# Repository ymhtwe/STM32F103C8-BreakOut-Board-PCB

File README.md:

# STM32F103C8-BreakOut-Board-PCB 

This repository contains the design files for a breakout board for the STM32F103C8T6 microcontroller in a 48-pin LQFP package. The breakout board provides easy access to all the pins of the microcontroller, as well as a USB-to-serial converter for programming and debugging.

Features
Compact breakout board for the STM32F103C8T6 microcontroller
All pins of the microcontroller are accessible via headers
Onboard 3.3V voltage regulator and decoupling capacitors
USB-to-serial converter for programming and debugging
Bootloader mode for easy firmware updates
Getting started
To get started with the STM32F103C8 Breakout Board PCB, you will need the following:

STM32F103C8T6 microcontroller (not included)
USB-to-serial cable (not included)
Development environment (e.g., STM32CubeIDE, Keil, or Arduino IDE)
To program and debug the microcontroller, connect the USB-to-serial cable to the J1 header on the breakout board, and connect the other end of the cable to your computer. Open your development environment and select the appropriate settings for the microcontroller and programming interface. You can then program and debug your firmware as usual.

Repository contents
Gerber/: Gerber files for manufacturing the PCB
Schematic/: Schematic and BOM for the PCB design
Hardware/: PCB layout design files in KiCad format
License
The STM32F103C8 Breakout Board PCB is released under the MIT License. See the LICENSE file for more details.

Credits
The STM32F103C8 Breakout Board PCB was designed by Ye Min Htwe. If you have any questions or feedback, please open an issue on GitHub.

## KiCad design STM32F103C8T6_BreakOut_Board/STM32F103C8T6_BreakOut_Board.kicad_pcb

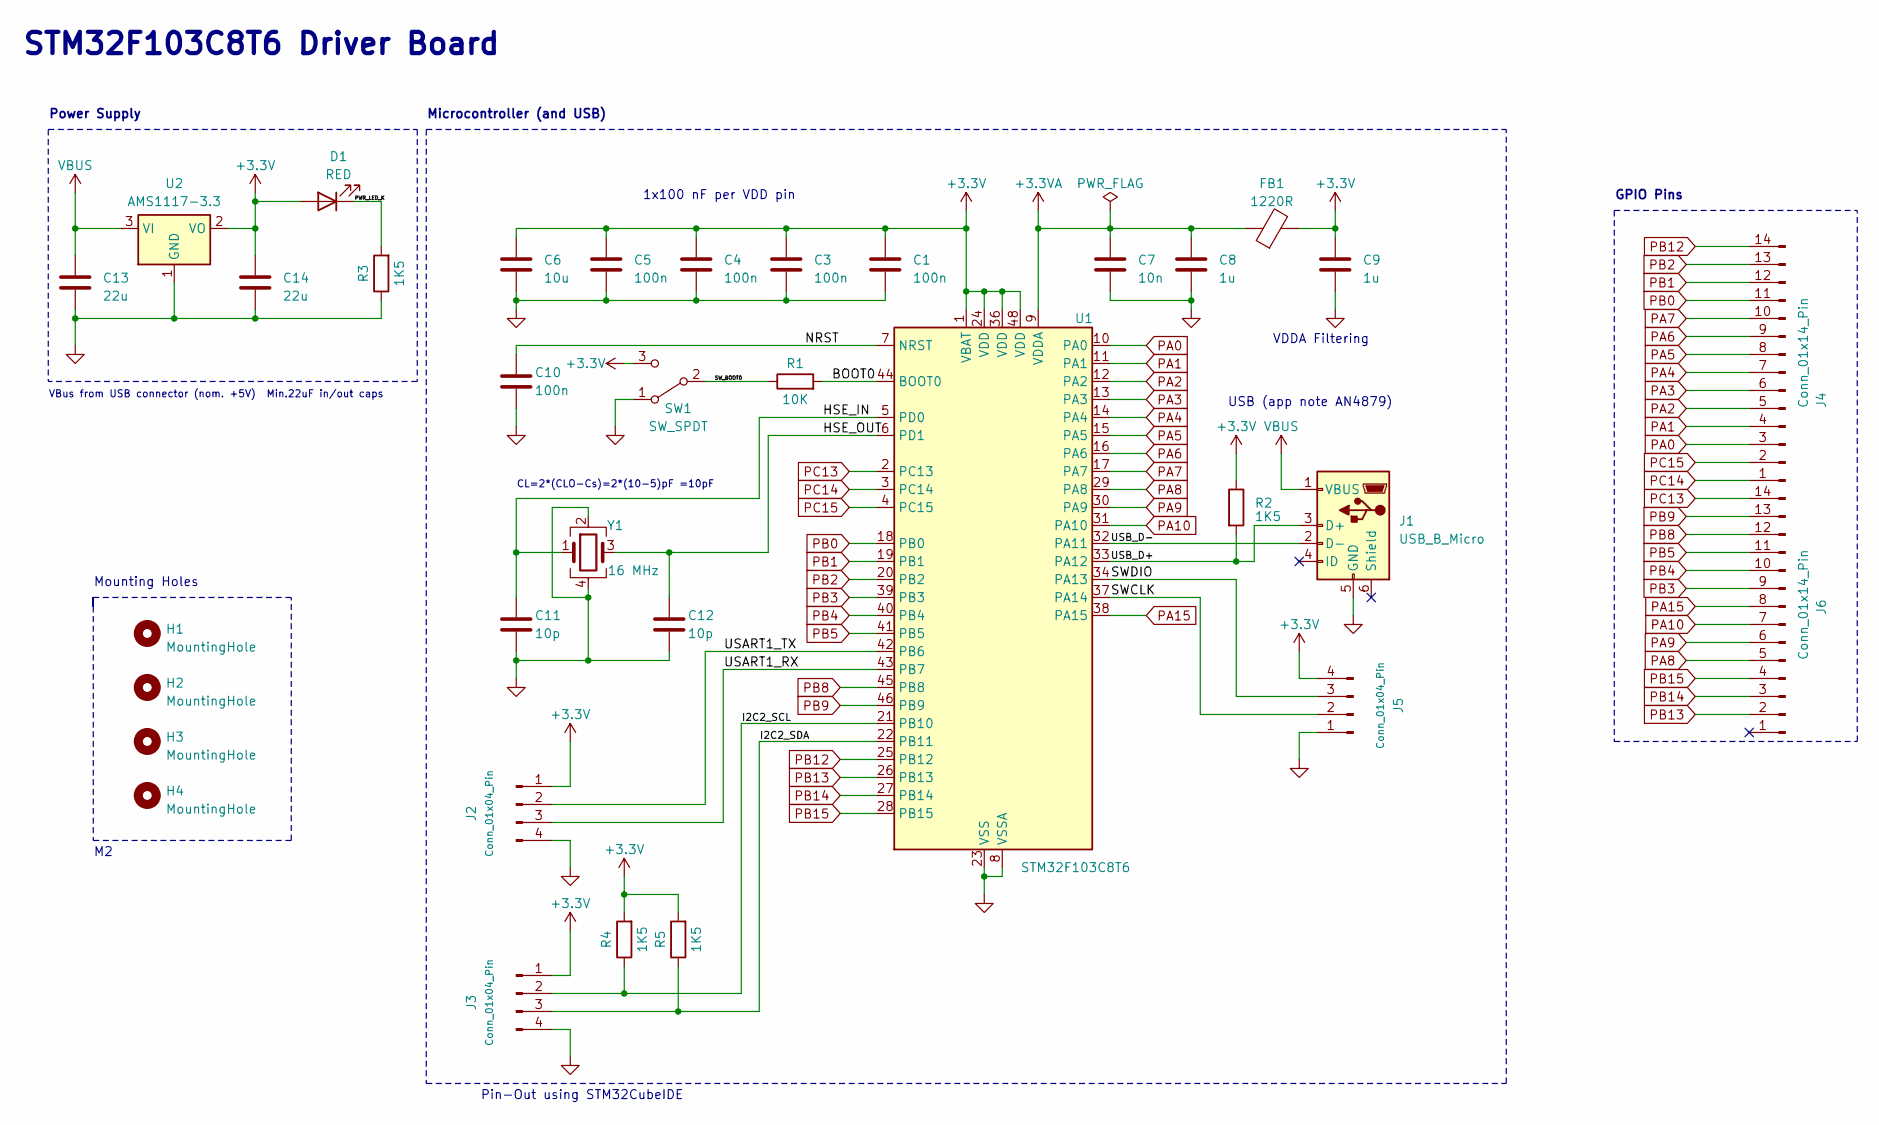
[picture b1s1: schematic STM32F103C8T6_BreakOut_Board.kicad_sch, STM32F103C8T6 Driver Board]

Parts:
C1, C3, C4, C5, C10: 100n; C_0402_1005Metric
C6: 10u; C_0603_1608Metric
C7: 10n; C_0402_1005Metric
C8, C9: 1u; C_0402_1005Metric
C11, C12: 10p; C_0402_1005Metric
C13, C14: 22u; C_0805_2012Metric
D1: RED; LED_0603_1608Metric
FB1: 1220R; L_0603_1608Metric
H1, H2, H3, H4: MountingHole; MountingHole_2.2mm_M2
J1: USB_B_Micro; USB_Micro-B_Wuerth_629105150521
J2, J3, J5: Conn_01x04_Pin; PinHeader_1x04_P2.54mm_Vertical
J4, J6: Conn_01x14_Pin; PinHeader_1x14_P2.54mm_Vertical
R1: 10K; R_0402_1005Metric
R2, R3, R4, R5: 1K5; R_0402_1005Metric
SW1: SW_SPDT; SW_SPDT_PCM12
U1: STM32F103C8T6; LQFP-48_7x7mm_P0.5mm
U2: AMS1117-3.3; SOT-223-3_TabPin2
Y1: 16 MHz; Crystal_SMD_3225-4Pin_3.2x2.5mm

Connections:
+3.3V: C1.1, C3.1, C4.1, C5.1, C6.1, C9.1, C14.1, D1.2 (A), FB1.2, J2.1, J3.1, J5.4, R2.1, R4.2, R5.2, SW1.3 (C), U1.1 (VBAT), U1.24 (VDD), U1.36 (VDD), U1.48 (VDD), U2.2 (VO)
+3.3VA: C7.1, C8.1, FB1.1, U1.9 (VDDA)
/BOOT0: R1.2, U1.44 (BOOT0)
/HSE_IN: C11.1, U1.5 (PD0), Y1.1
/HSE_OUT: C12.1, U1.6 (PD1), Y1.3
/I2C2_SCL: J3.2, R4.1, U1.21 (PB10)
/I2C2_SDA: J3.3, R5.1, U1.22 (PB11)
/NRST: C10.1, U1.7 (NRST)
/PWR_LED_K: D1.1 (K), R3.2
/SWCLK: J5.2, U1.37 (PA14)
/SWDIO: J5.3, U1.34 (PA13)
/SW_BOOT0: R1.1, SW1.2 (B)
/USART1_RX: J2.3, U1.43 (PB7)
/USART1_TX: J2.2, U1.42 (PB6)
/USB_D+: J1.3 (D+), R2.2, U1.33 (PA12)
/USB_D-: J1.2 (D-), U1.32 (PA11)
GND: C1.2, C3.2, C4.2, C5.2, C6.2, C7.2, C8.2, C9.2, C10.2, C11.2, C12.2, C13.2, C14.2, J1.5 (GND), J2.4, J3.4, J5.1, R3.1, SW1.1 (A), U1.8 (VSSA), U1.23 (VSS), U1.35 (VSS), U1.47 (VSS), U2.1 (GND), Y1.2, Y1.4
PA0: J4.3, U1.10 (PA0)
PA1: J4.4, U1.11 (PA1)
PA2: J4.5, U1.12 (PA2)
PA3: J4.6, U1.13 (PA3)
PA4: J4.7, U1.14 (PA4)
PA5: J4.8, U1.15 (PA5)
PA6: J4.9, U1.16 (PA6)
PA7: J4.10, U1.17 (PA7)
PA8: J6.5, U1.29 (PA8)
PA9: J6.6, U1.30 (PA9)
PA10: J6.7, U1.31 (PA10)
PA15: J6.8, U1.38 (PA15)
PB0: J4.11, U1.18 (PB0)
PB1: J4.12, U1.19 (PB1)
PB2: J4.13, U1.20 (PB2)
PB3: J6.9, U1.39 (PB3)
PB4: J6.10, U1.40 (PB4)
PB5: J6.11, U1.41 (PB5)
PB8: J6.12, U1.45 (PB8)
PB9: J6.13, U1.46 (PB9)
PB12: J4.14, U1.25 (PB12)
PB13: J6.2, U1.26 (PB13)
PB14: J6.3, U1.27 (PB14)
PB15: J6.4, U1.28 (PB15)
PC13: J6.14, U1.2 (PC13)
PC14: J4.1, U1.3 (PC14)
PC15: J4.2, U1.4 (PC15)
VBUS: C13.1, J1.1 (VBUS), U2.3 (VI)

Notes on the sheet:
Microcontroller (and USB)
VDDA Filtering
STM32F103C8T6 Driver Board
Mounting Holes
Pin-Out using STM32CubeIDE
GPIO Pins
Power Supply
VBus from USB connector (nom. +5V) Min.22uF in/out caps
USB (app note AN4879)
1x100 nF per VDD pin
CL=2*(CLO-Cs)=2*(10-5)pF =10pF

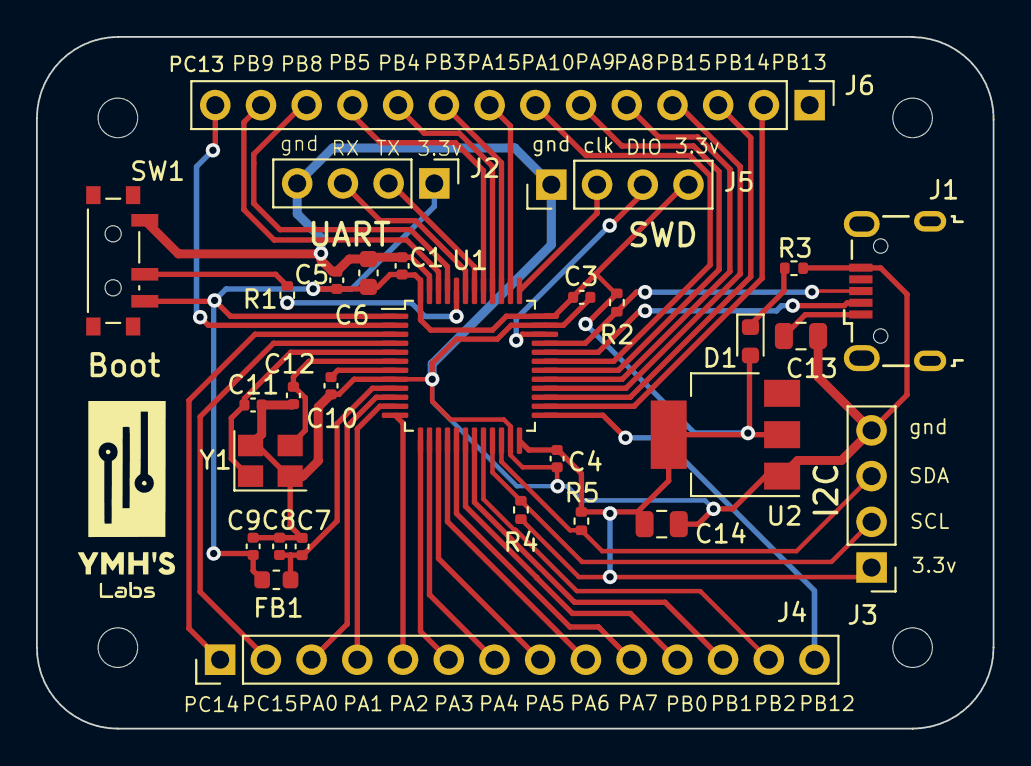
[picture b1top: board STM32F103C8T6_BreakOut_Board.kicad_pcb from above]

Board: 2 copper layers, 53.2 x 38.4 mm, 34 parts (0 on the bottom side), 45 nets.

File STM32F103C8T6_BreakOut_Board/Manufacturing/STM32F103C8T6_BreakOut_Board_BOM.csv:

"Source:","E:\KiCad\Projects\STM32F103C8T6_BreakOut_Board\STM32F103C8T6_BreakOut_Board.kicad_sch"
"Date:","2/16/2023 3:16:33 AM"
"Tool:","Eeschema (7.0.0)"
"Generator:","E:\KiCad\7.0\bin\scripting\plugins/bom_csv_grouped_by_value_with_fp.py"
"Component Count:","34"
"Ref","Qnty","Value","Cmp name","Footprint","Description","Vendor","DNP"
"C1, C3, C4, C5, C10","5","100n","C","Capacitor_SMD:C_0402_1005Metric","Unpolarized capacitor","",""
"C6","1","10u","C","Capacitor_SMD:C_0603_1608Metric","Unpolarized capacitor","",""
"C7","1","10n","C","Capacitor_SMD:C_0402_1005Metric","Unpolarized capacitor","",""
"C8, C9","2","1u","C","Capacitor_SMD:C_0402_1005Metric","Unpolarized capacitor","",""
"C11, C12","2","10p","C","Capacitor_SMD:C_0402_1005Metric","Unpolarized capacitor","",""
"C13, C14","2","22u","C","Capacitor_SMD:C_0805_2012Metric","Unpolarized capacitor","",""
"D1","1","RED","LED","LED_SMD:LED_0603_1608Metric","Light emitting diode","",""
"FB1","1","1220R","FerriteBead","Inductor_SMD:L_0603_1608Metric","Ferrite bead","",""
"H1, H2, H3, H4","4","MountingHole","MountingHole","MountingHole:MountingHole_2.2mm_M2","Mounting Hole without connection","",""
"J1","1","USB_B_Micro","USB_B_Micro","Connector_USB:USB_Micro-B_Wuerth_629105150521","USB Micro Type B connector","",""
"J2, J3, J5","3","Conn_01x04_Pin","Conn_01x04_Pin","Connector_PinHeader_2.54mm:PinHeader_1x04_P2.54mm_Vertical","Generic connector, single row, 01x04, script generated","",""
"J4, J6","2","Conn_01x14_Pin","Conn_01x14_Pin","Connector_PinHeader_2.54mm:PinHeader_1x14_P2.54mm_Vertical","Generic connector, single row, 01x14, script generated","",""
"R1","1","10K","R","Resistor_SMD:R_0402_1005Metric","Resistor","",""
"R2, R3, R4, R5","4","1K5","R","Resistor_SMD:R_0402_1005Metric","Resistor","",""
"SW1","1","SW_SPDT","SW_SPDT","Button_Switch_SMD:SW_SPDT_PCM12","Switch, single pole double throw","",""
"U1","1","STM32F103C8T6","STM32F103C8Tx","Package_QFP:LQFP-48_7x7mm_P0.5mm","STMicroelectronics Arm Cortex-M3 MCU, 64KB flash, 20KB RAM, 72 MHz, 2.0-3.6V, 37 GPIO, LQFP48","",""
"U2","1","AMS1117-3.3","AMS1117-3.3","Package_TO_SOT_SMD:SOT-223-3_TabPin2","1A Low Dropout regulator, positive, 3.3V fixed output, SOT-223","",""
"Y1","1","16 MHz","Crystal_GND24","Crystal:Crystal_SMD_3225-4Pin_3.2x2.5mm","Four pin crystal, GND on pins 2 and 4","",""
